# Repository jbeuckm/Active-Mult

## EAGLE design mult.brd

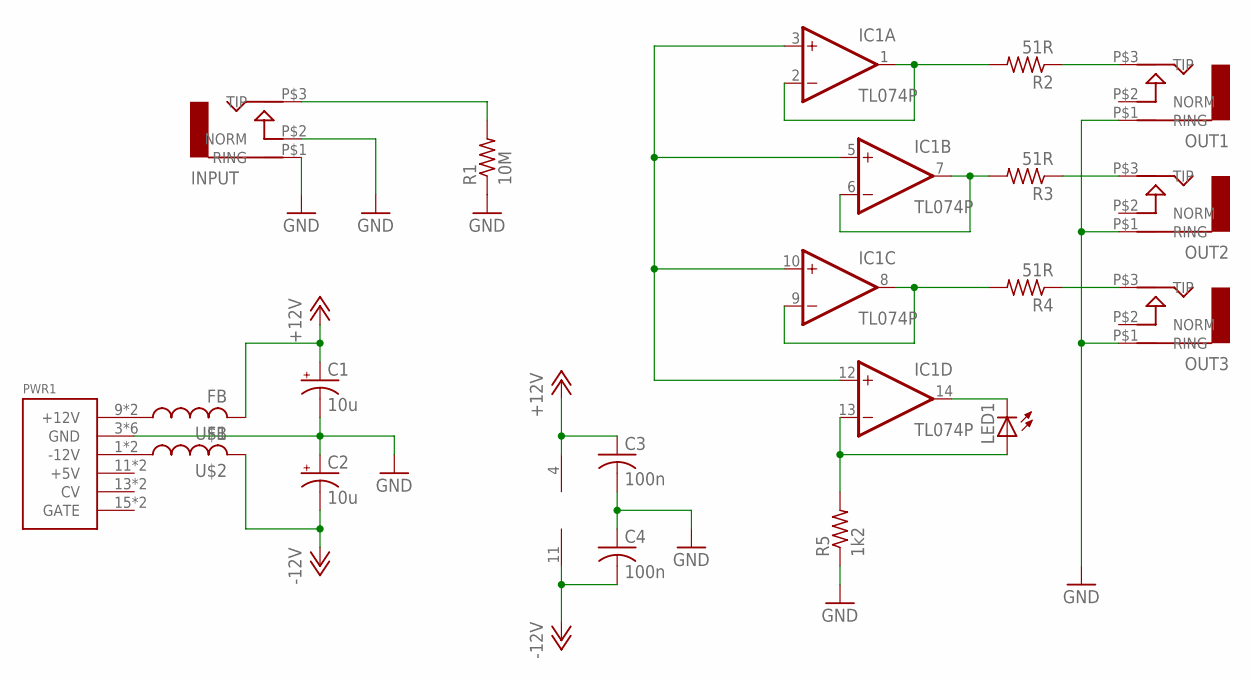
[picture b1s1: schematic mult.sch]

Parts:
C1, C2: 10u; B45181A
C3, C4: 100n; C050-024X044
IC1: TL074P; DIL14
INPUT: AUDIO-JACK; ERTHENVAR-JACK-90DEG
LED1: LED5MM
OUT1, OUT2, OUT3: AUDIO-JACK; ERTHENVAR-JACK-90DEG
PWR1: POWER; POWER_16
R1: 10M; 0207/10
R2, R3, R4: 51R; 0207/10
R5: 1k2; 0207/10
U$1, U$2: FB

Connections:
+12V: C1.+, C3.1, IC1.4 (V+), U$1.P$2 (2)
-12V: C2.-, C4.2, IC1.11 (V-), U$2.P$2 (2)
GND: C1.-, C2.+, C3.2, C4.1, INPUT.P$1 (RING), INPUT.P$2 (NORM), OUT1.P$1 (RING), OUT2.P$1 (RING), OUT3.P$1 (RING), PWR1.3 (GND), PWR1.4 (GND), PWR1.5 (GND), PWR1.6 (GND), PWR1.7 (GND), PWR1.8 (GND), R1.1, R5.1
unnamed: PWR1.9 (+12V), PWR1.10 (+12V), U$1.P$1 (1)
unnamed: PWR1.1 (-12V), PWR1.2 (-12V), U$2.P$1 (1)
unnamed: OUT1.P$3 (TIP), R2.1
unnamed: OUT2.P$3 (TIP), R3.1
unnamed: OUT3.P$3 (TIP), R4.1
unnamed: IC1.3 (+IN), IC1.5 (+IN), IC1.10 (+IN), IC1.12 (+IN)
unnamed: IC1.1 (OUT), IC1.2 (-IN), R2.2
unnamed: IC1.6 (-IN), IC1.7 (OUT), R3.2
unnamed: IC1.8 (OUT), IC1.9 (-IN), R4.2
unnamed: IC1.14 (OUT), LED1.K (C)
unnamed: IC1.13 (-IN), LED1.A, R5.2
unnamed: INPUT.P$3 (TIP), R1.2

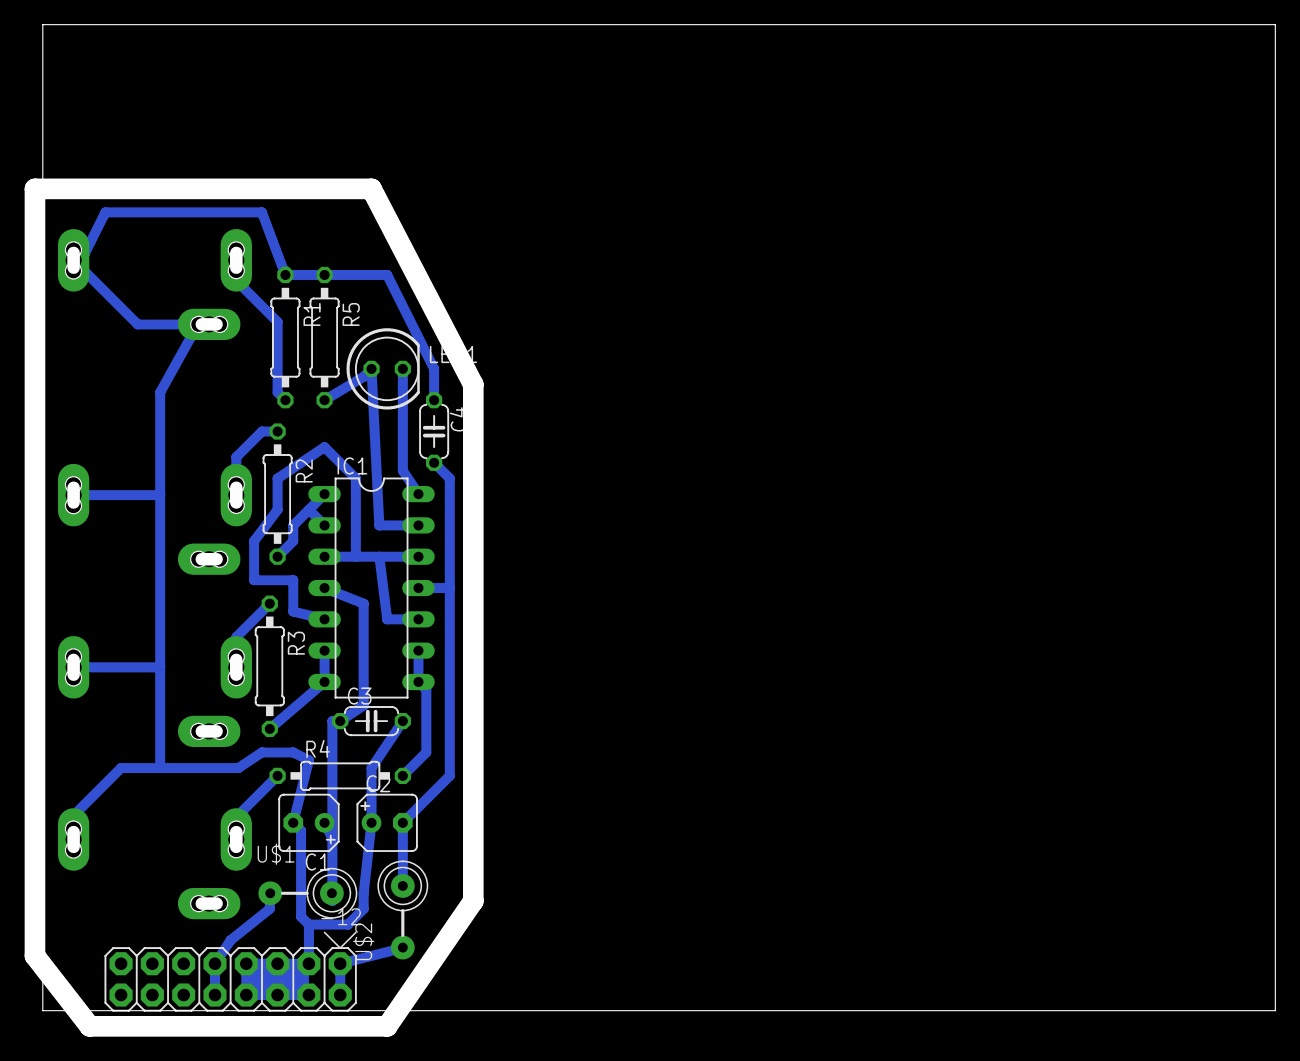
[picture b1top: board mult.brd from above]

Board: 2 copper layers, 99.8 x 80.4 mm, 18 parts (0 on the bottom side), 15 nets.

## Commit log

2015-12-31 gcode
2015-12-31 rectangle onto the power connector
2016-02-02 starting the panel
2016-02-02 panel gcode
2016-11-01 actually connected input jack duh
